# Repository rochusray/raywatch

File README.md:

# Raywatch
**An open-source, privacy-first smart(_er_)watch designed to be an all day, every day companion to help you navigate your way trugh life.**
> **Project status:** Early-stage development.

## Why Raywatch?
Most smartwatches are designed as an extension to your phone. Raywatch is build different.
## Core principles
- **Longevity:** Raywatch is meant to be a robust, long living, repairable, watertight, reliable device.
- **Independence:** Raywatch aims to be completely independent from the power grid, as well as the internet or other centralized networks.
- **Security & Privacy:** A core requirement is that Raywatch must be a secure device at all times. It will feature a [TPM](https://en.wikipedia.org/wiki/Trusted_Platform_Module), used for providing a key vault with integrated anti tampering protections, as well as encryption and decryption of sensible data and messages. Raywatch is meant to be a cryptographic fortress, build to resist. Also, Raywatch will never store or share any data without direct consent.
- **Open Source:** The Raywatch project is open source under an ethical license. Therefore it is - and will always be - open for anyone to contribute, modify or check the software and hardware.
- **Affordability:** Raywatch is aimed to be as affordable as possible. The current plan is to price it around 250€.

## Applications
- **Resistance:** Raywatch is build to not only resist against cyber attacks, but also to aid in resistance against oppression, repression, regimes and cooperations.
- **Physical Health & Disabilities:** Raywatch has multiple builtin sensors to be able to collect and analyze data about your physical health, while also never sharing it with your health insurance. It shall also provide assistance for people with disabilities.
- **Mental Health & Neurodivergents:** Raywatch started out with the purpose of tracking mental health symptoms, to detect patterns and assist therapy. This is still a prime functionality, as well as providing additional features to aid people in their lives with physical illnesses and neurodivergents.
- **Communication:** In groups, Raywatches are able to communicate via the [Meshtastic](https://meshtastic.org/) network, but separately encrypted. For maximum security it will be possible to do a local key exchange via NFC.

## Hardware Features
Here is a list of hardware features Raywatch is planned to have:
- TPM
- MicroSD card slot
- Multiple high accuracy accelerometers for acceleration and position tracking
- 3-Axis magnetometer for orientation sensing
- Heart rate & O₂ blood level sensor
- 10 buttons
- Transflective RGB LCD display
- ~60 RGB LEDs 
- BLE (_Bluetooth Low Energy_) to connect to your phone
- Meshtastic & LoRa for independend communication
- Vibration motor for discrete notifications
- 200mAh replacable battery
- NFC
- Wireless charging
- Solar powered charging

## About Us
We are a small developer collective based in Munich, Germany.
### Our Values
- **Against Discrimination:** We are completely against any kind of discrimination, including but not limited to racism, sexism, classism, ableism, and any discrimination against the LGBTQIA+ community and it's members.
- **Against Fascism:** We are openly against fascism and any fascist regime.
- **Against Exploitation:** We are strongly against any kind of exploitation of any human beings or other feeling beings.
- **Openness:** All information should be public, except private information.

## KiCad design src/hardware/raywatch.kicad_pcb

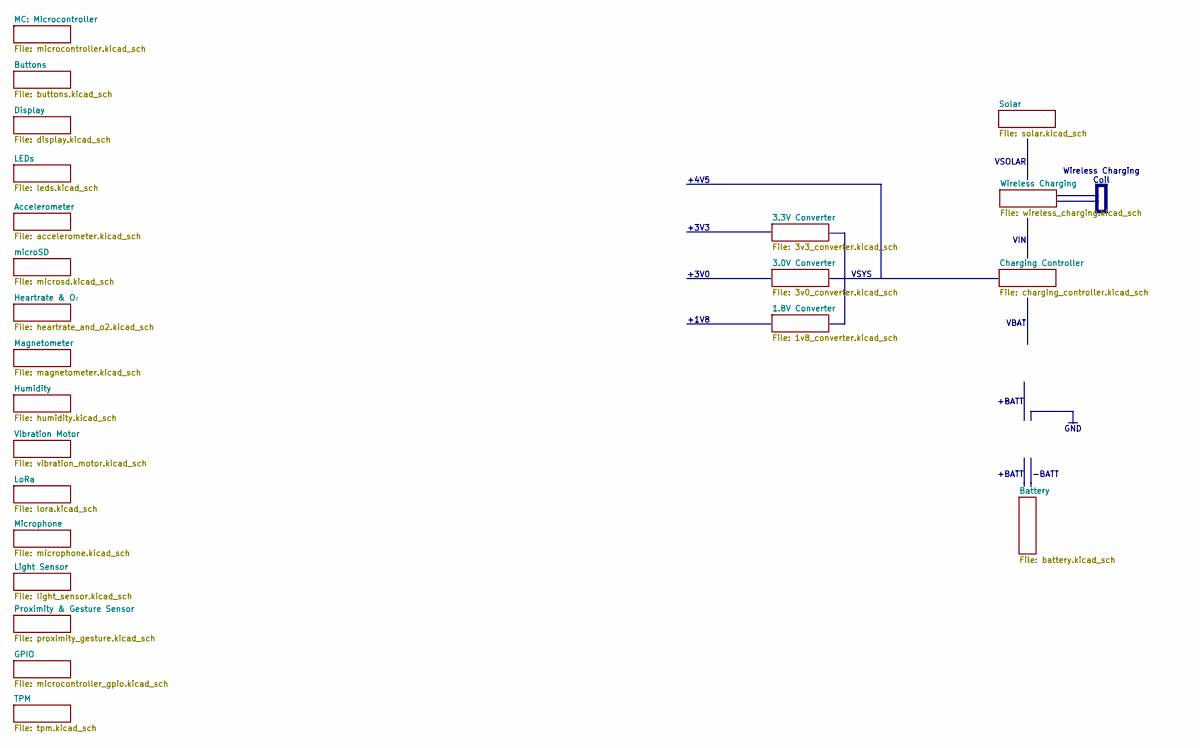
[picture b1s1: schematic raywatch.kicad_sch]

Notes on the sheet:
+BATT
-BATT
VIN
+3V0
VSOLAR
+4V5
+3V3
GND
VBAT
VSYS
+1V8
Wireless Charging Coil

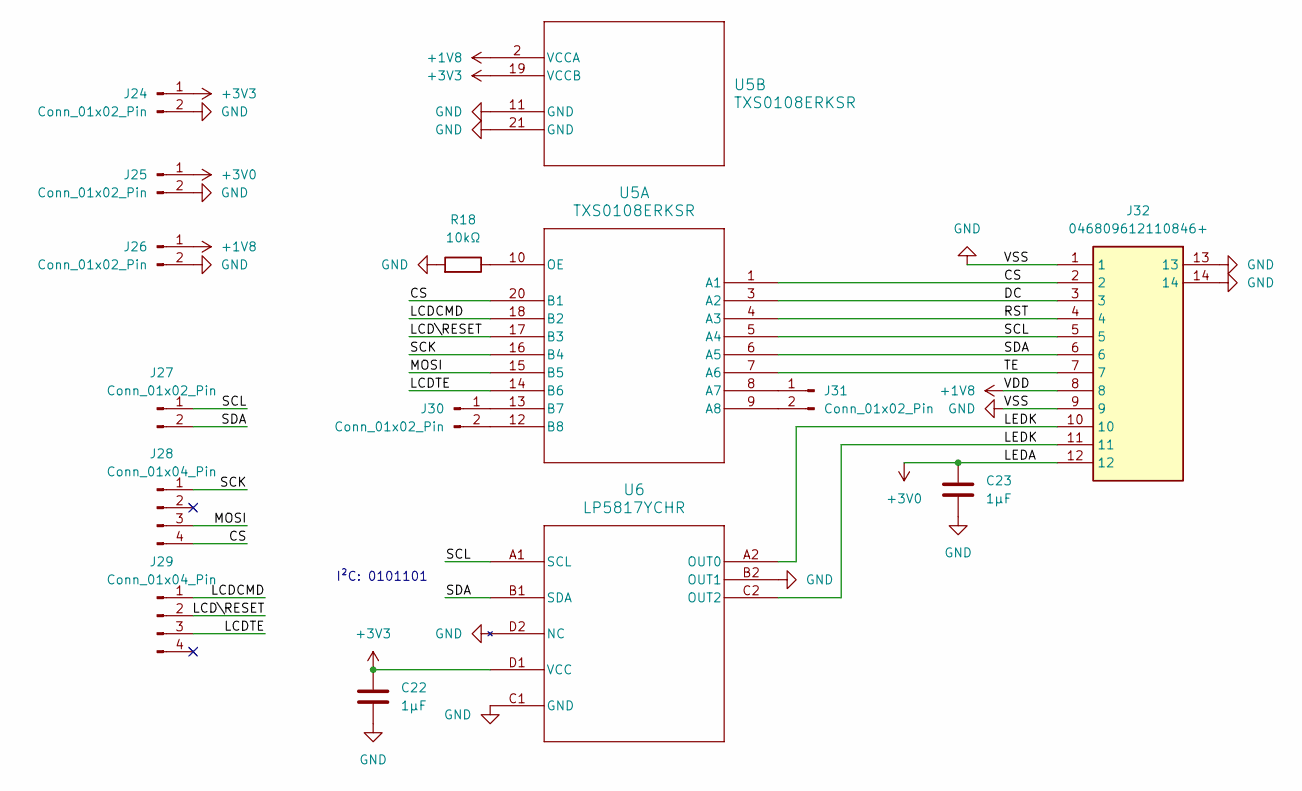
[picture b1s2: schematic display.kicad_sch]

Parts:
C22: 1µF; C_0402_1005Metric
C23: 1µF; C_0402_1005Metric; Rated voltage 10V
J24, J25, J26, J27, J30, J31: Conn_01x02_Pin; PinHeader_1x02_P1.27mm_Vertical
J28, J29: Conn_01x04_Pin; PinHeader_1x04_P1.27mm_Vertical
J32: 046809612110846+; 046809612110846; Manufacturer_Part_Number 046809612110846+; Mouser Part Number 346-046809612110846+
R18: 10kΩ; R_0402_1005Metric
U5: TXS0108ERKSR; VQFN20_RKS_TEX
U6: LP5817YCHR; DSBGA-8_YCH0008_TEX

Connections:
+3V0: C23.1, J25.1, J32.12; also elsewhere on the board
/Display/CS: J28.4, J32.2, U5.1 (A1), U5.20 (B1)
/Display/DC: J32.3, U5.3 (A2)
/Display/LCDCMD: J29.1, U5.18 (B2)
/Display/LCDTE: J29.3, U5.14 (B6)
/Display/LCD\RESET: J29.2, U5.17 (B3)
/Display/LEDK: J32.10, J32.11, U6.A2 (OUT0), U6.C2 (OUT2)
/Display/MOSI: J28.3, U5.15 (B5)
/Display/RST: J32.4, U5.4 (A3)
/Display/SCK: J28.1, U5.16 (B4)
/Display/SCL: J27.1, J32.5, U5.5 (A4), U6.A1 (SCL)
/Display/SDA: J27.2, J32.6, U5.6 (A5), U6.B1 (SDA)
/Display/TE: J32.7, U5.7 (A6)
GND: C22.2, C23.2, J24.2, J25.2, J26.2, J32.1, J32.9, J32.13, J32.14, R18.2, U5.11 (GND), U5.21 (GND), U6.B2 (OUT1), U6.C1 (GND), U6.D2 (NC); also elsewhere on the board
unnamed: J30.1, U5.13 (B7)
unnamed: J30.2, U5.12 (B8)
unnamed: J31.1, U5.8 (A7)
unnamed: J31.2, U5.9 (A8)
unnamed: R18.1, U5.10 (OE)

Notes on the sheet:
I²C: 0101101

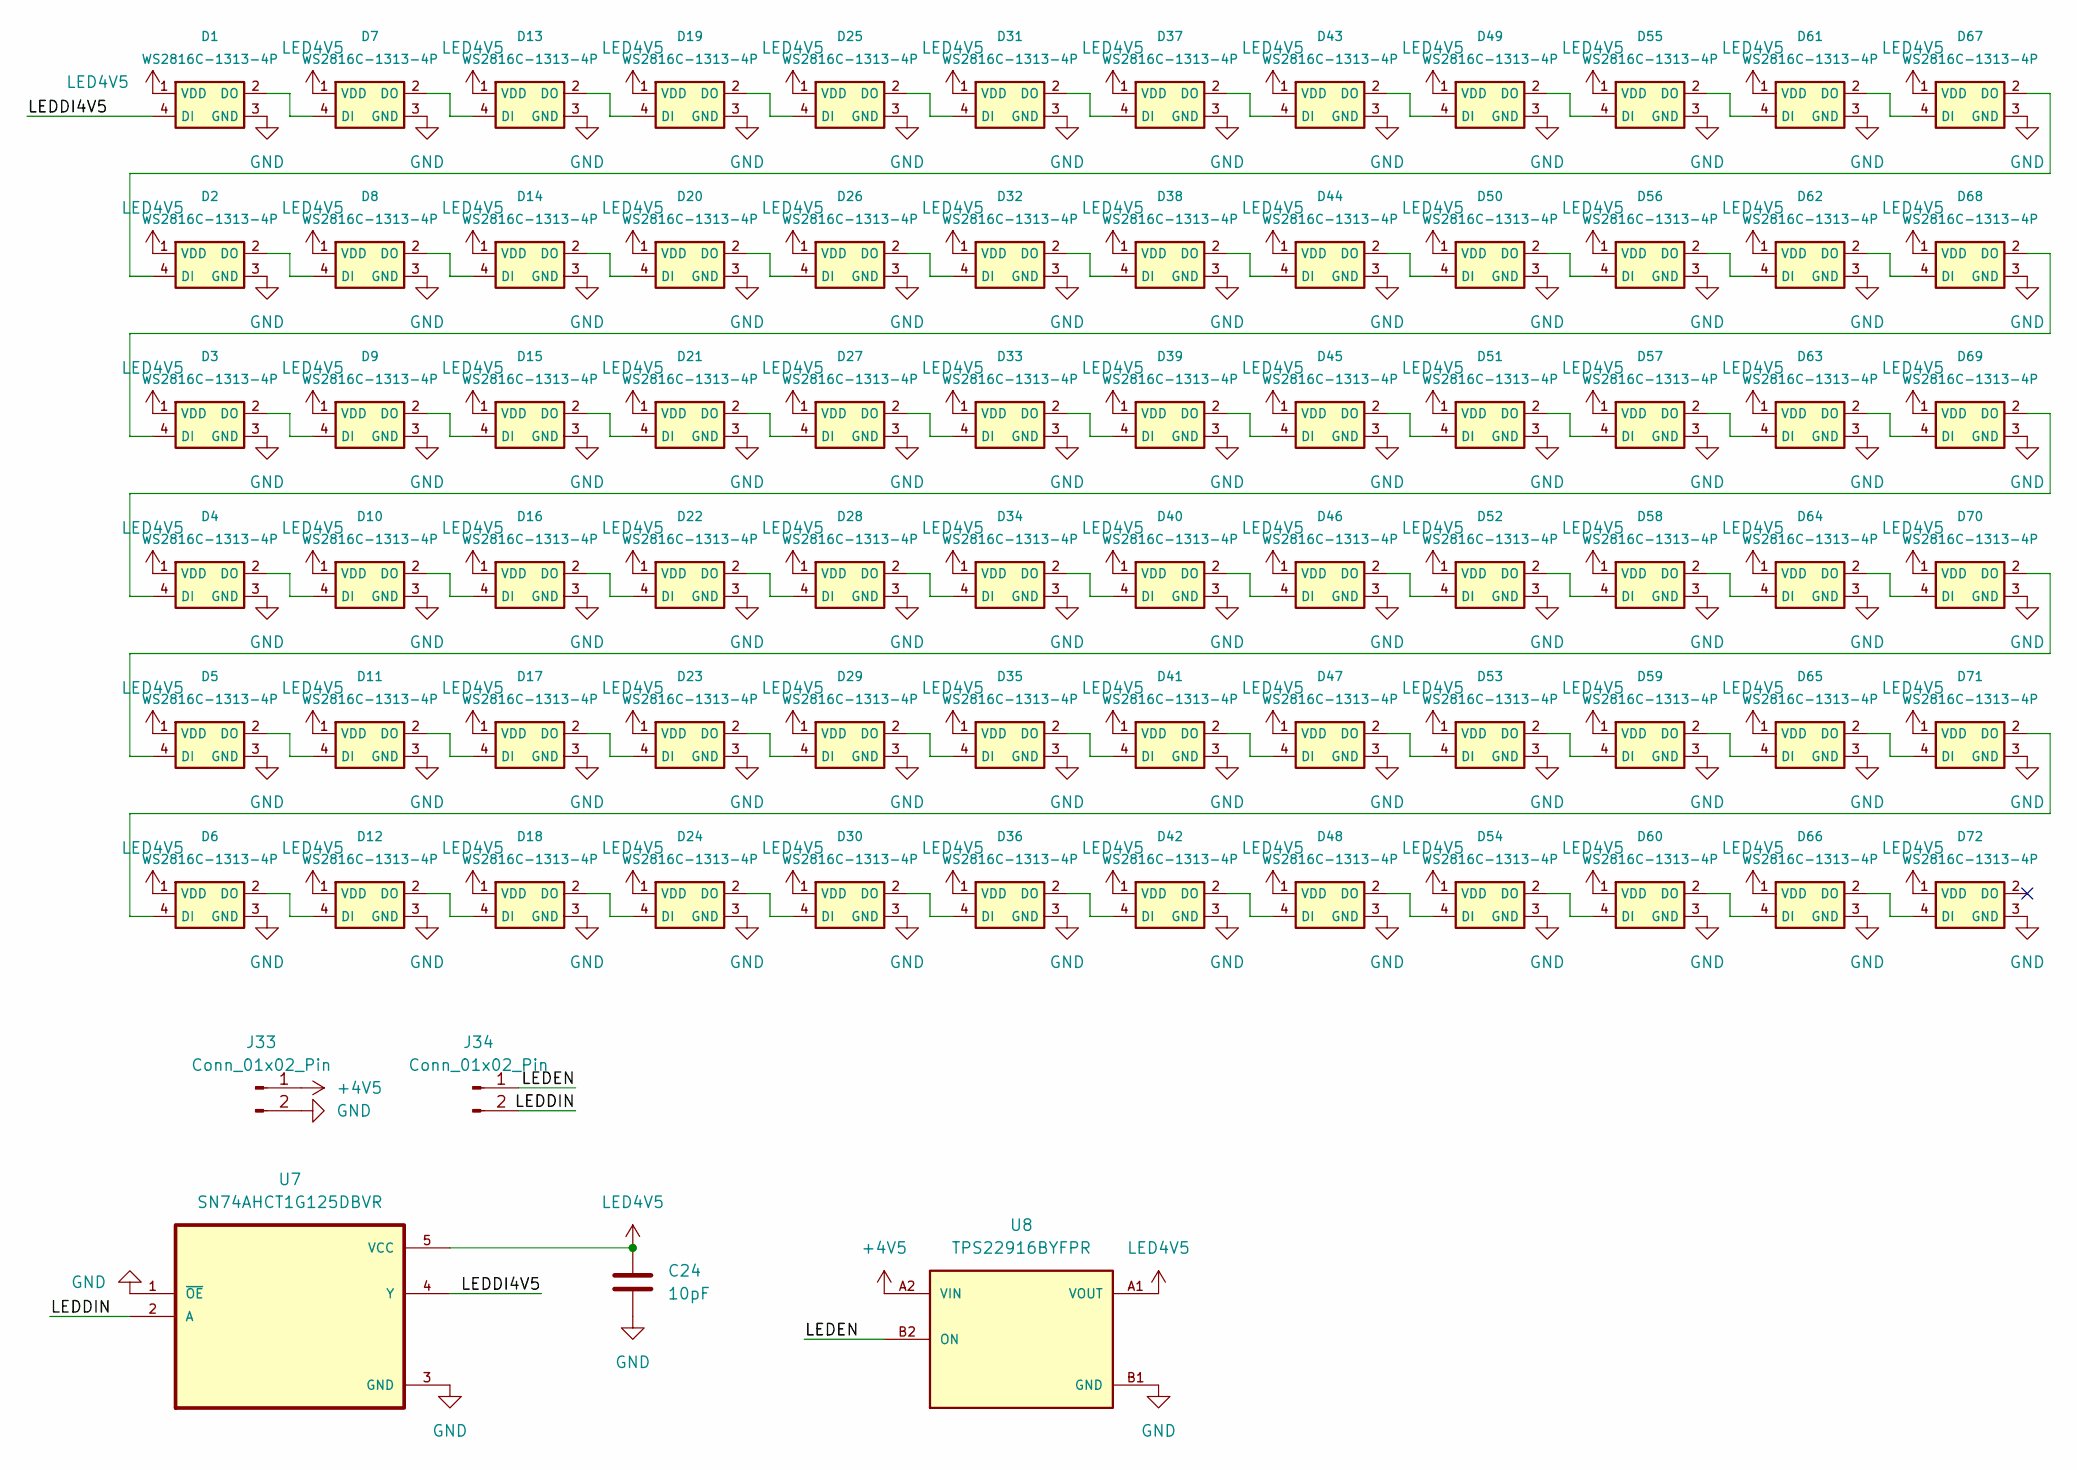
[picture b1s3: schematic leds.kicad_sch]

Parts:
C24: 10pF; C_0402_1005Metric
D1, D2, D3, D4, D5, D6, D7, D8, D9, D10, D11, D12, D13, D14, D15, D16, D17, D18, D19, D20, D21, D22, D23, D24, D25, D26, D27, D28, D29, D30, D31, D32, D33, D34, D35, D36, D37, D38, D39, D40, D41, D42, D43, D44, D45, D46, D47, D48, D49, D50, D51, D52, D53, D54, D55, D56, D57, D58, D59, D60, D61, D62, D63, D64, D65, D66, D67, D68, D69, D70, D71, D72: WS2816C-1313-4P
J33, J34: Conn_01x02_Pin; PinHeader_1x02_P1.27mm_Vertical
U7: SN74AHCT1G125DBVR; SOT95P280X145-5N
U8: TPS22916BYFPR; IC_TPS22916BYFPR; PARTREV F

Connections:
+4V5: J33.1, U8.A2 (VIN); also elsewhere on the board
/LEDs/LEDDI4V5: D1.4 (DI), U7.4 (Y)
/LEDs/LEDDIN: J34.2, U7.2 (A)
/LEDs/LEDEN: J34.1, U8.B2 (ON)
GND: C24.2, D1.3 (GND), D2.3 (GND), D3.3 (GND), D4.3 (GND), D5.3 (GND), D6.3 (GND), D7.3 (GND), D8.3 (GND), D9.3 (GND), D10.3 (GND), D11.3 (GND), D12.3 (GND), D13.3 (GND), D14.3 (GND), D15.3 (GND), D16.3 (GND), D17.3 (GND), D18.3 (GND), D19.3 (GND), D20.3 (GND), D21.3 (GND), D22.3 (GND), D23.3 (GND), D24.3 (GND), D25.3 (GND), D26.3 (GND), D27.3 (GND), D28.3 (GND), D29.3 (GND), D30.3 (GND), D31.3 (GND), D32.3 (GND), D33.3 (GND), D34.3 (GND), D35.3 (GND), D36.3 (GND), D37.3 (GND), D38.3 (GND), D39.3 (GND), D40.3 (GND), D41.3 (GND), D42.3 (GND), D43.3 (GND), D44.3 (GND), D45.3 (GND), D46.3 (GND), D47.3 (GND), D48.3 (GND), D49.3 (GND), D50.3 (GND), D51.3 (GND), D52.3 (GND), D53.3 (GND), D54.3 (GND), D55.3 (GND), D56.3 (GND), D57.3 (GND), D58.3 (GND), D59.3 (GND), D60.3 (GND), D61.3 (GND), D62.3 (GND), D63.3 (GND), D64.3 (GND), D65.3 (GND), D66.3 (GND), D67.3 (GND), D68.3 (GND), D69.3 (GND), D70.3 (GND), D71.3 (GND), D72.3 (GND), J33.2, U7.1 (~OE), U7.3 (GND), U8.B1 (GND); also elsewhere on the board
LED4V5: C24.1, D1.1 (VDD), D2.1 (VDD), D3.1 (VDD), D4.1 (VDD), D5.1 (VDD), D6.1 (VDD), D7.1 (VDD), D8.1 (VDD), D9.1 (VDD), D10.1 (VDD), D11.1 (VDD), D12.1 (VDD), D13.1 (VDD), D14.1 (VDD), D15.1 (VDD), D16.1 (VDD), D17.1 (VDD), D18.1 (VDD), D19.1 (VDD), D20.1 (VDD), D21.1 (VDD), D22.1 (VDD), D23.1 (VDD), D24.1 (VDD), D25.1 (VDD), D26.1 (VDD), D27.1 (VDD), D28.1 (VDD), D29.1 (VDD), D30.1 (VDD), D31.1 (VDD), D32.1 (VDD), D33.1 (VDD), D34.1 (VDD), D35.1 (VDD), D36.1 (VDD), D37.1 (VDD), D38.1 (VDD), D39.1 (VDD), D40.1 (VDD), D41.1 (VDD), D42.1 (VDD), D43.1 (VDD), D44.1 (VDD), D45.1 (VDD), D46.1 (VDD), D47.1 (VDD), D48.1 (VDD), D49.1 (VDD), D50.1 (VDD), D51.1 (VDD), D52.1 (VDD), D53.1 (VDD), D54.1 (VDD), D55.1 (VDD), D56.1 (VDD), D57.1 (VDD), D58.1 (VDD), D59.1 (VDD), D60.1 (VDD), D61.1 (VDD), D62.1 (VDD), D63.1 (VDD), D64.1 (VDD), D65.1 (VDD), D66.1 (VDD), D67.1 (VDD), D68.1 (VDD), D69.1 (VDD), D70.1 (VDD), D71.1 (VDD), D72.1 (VDD), U7.5 (VCC), U8.A1 (VOUT)
unnamed: D1.2 (DO), D7.4 (DI)
unnamed: D2.4 (DI), D67.2 (DO)
unnamed: D2.2 (DO), D8.4 (DI)
unnamed: D3.4 (DI), D68.2 (DO)
unnamed: D3.2 (DO), D9.4 (DI)
unnamed: D4.4 (DI), D69.2 (DO)
unnamed: D5.4 (DI), D70.2 (DO)
unnamed: D6.4 (DI), D71.2 (DO)
unnamed: D4.2 (DO), D10.4 (DI)
unnamed: D10.2 (DO), D16.4 (DI)
unnamed: D5.2 (DO), D11.4 (DI)
unnamed: D11.2 (DO), D17.4 (DI)
unnamed: D6.2 (DO), D12.4 (DI)
unnamed: D12.2 (DO), D18.4 (DI)
unnamed: D7.2 (DO), D13.4 (DI)
unnamed: D13.2 (DO), D19.4 (DI)
unnamed: D8.2 (DO), D14.4 (DI)
unnamed: D14.2 (DO), D20.4 (DI)
unnamed: D9.2 (DO), D15.4 (DI)
unnamed: D15.2 (DO), D21.4 (DI)
unnamed: D16.2 (DO), D22.4 (DI)
unnamed: D17.2 (DO), D23.4 (DI)
unnamed: D18.2 (DO), D24.4 (DI)
unnamed: D19.2 (DO), D25.4 (DI)
unnamed: D20.2 (DO), D26.4 (DI)
unnamed: D21.2 (DO), D27.4 (DI)
unnamed: D22.2 (DO), D28.4 (DI)
unnamed: D23.2 (DO), D29.4 (DI)
unnamed: D24.2 (DO), D30.4 (DI)
unnamed: D25.2 (DO), D31.4 (DI)
unnamed: D26.2 (DO), D32.4 (DI)
unnamed: D27.2 (DO), D33.4 (DI)
unnamed: D28.2 (DO), D34.4 (DI)
unnamed: D29.2 (DO), D35.4 (DI)
unnamed: D30.2 (DO), D36.4 (DI)
unnamed: D31.2 (DO), D37.4 (DI)
unnamed: D32.2 (DO), D38.4 (DI)
unnamed: D33.2 (DO), D39.4 (DI)
unnamed: D34.2 (DO), D40.4 (DI)
unnamed: D35.2 (DO), D41.4 (DI)
unnamed: D36.2 (DO), D42.4 (DI)
unnamed: D37.2 (DO), D43.4 (DI)
unnamed: D38.2 (DO), D44.4 (DI)
unnamed: D39.2 (DO), D45.4 (DI)
unnamed: D40.2 (DO), D46.4 (DI)
unnamed: D41.2 (DO), D47.4 (DI)
unnamed: D42.2 (DO), D48.4 (DI)
unnamed: D43.2 (DO), D49.4 (DI)
unnamed: D44.2 (DO), D50.4 (DI)
unnamed: D45.2 (DO), D51.4 (DI)
unnamed: D46.2 (DO), D52.4 (DI)
unnamed: D47.2 (DO), D53.4 (DI)
unnamed: D48.2 (DO), D54.4 (DI)
unnamed: D49.2 (DO), D55.4 (DI)
unnamed: D50.2 (DO), D56.4 (DI)
unnamed: D51.2 (DO), D57.4 (DI)
unnamed: D52.2 (DO), D58.4 (DI)
unnamed: D53.2 (DO), D59.4 (DI)
unnamed: D54.2 (DO), D60.4 (DI)
unnamed: D55.2 (DO), D61.4 (DI)
unnamed: D56.2 (DO), D62.4 (DI)
unnamed: D57.2 (DO), D63.4 (DI)
unnamed: D58.2 (DO), D64.4 (DI)
unnamed: D59.2 (DO), D65.4 (DI)
unnamed: D60.2 (DO), D66.4 (DI)
unnamed: D61.2 (DO), D67.4 (DI)
unnamed: D62.2 (DO), D68.4 (DI)
unnamed: D63.2 (DO), D69.4 (DI)
unnamed: D64.2 (DO), D70.4 (DI)
unnamed: D65.2 (DO), D71.4 (DI)
unnamed: D66.2 (DO), D72.4 (DI)

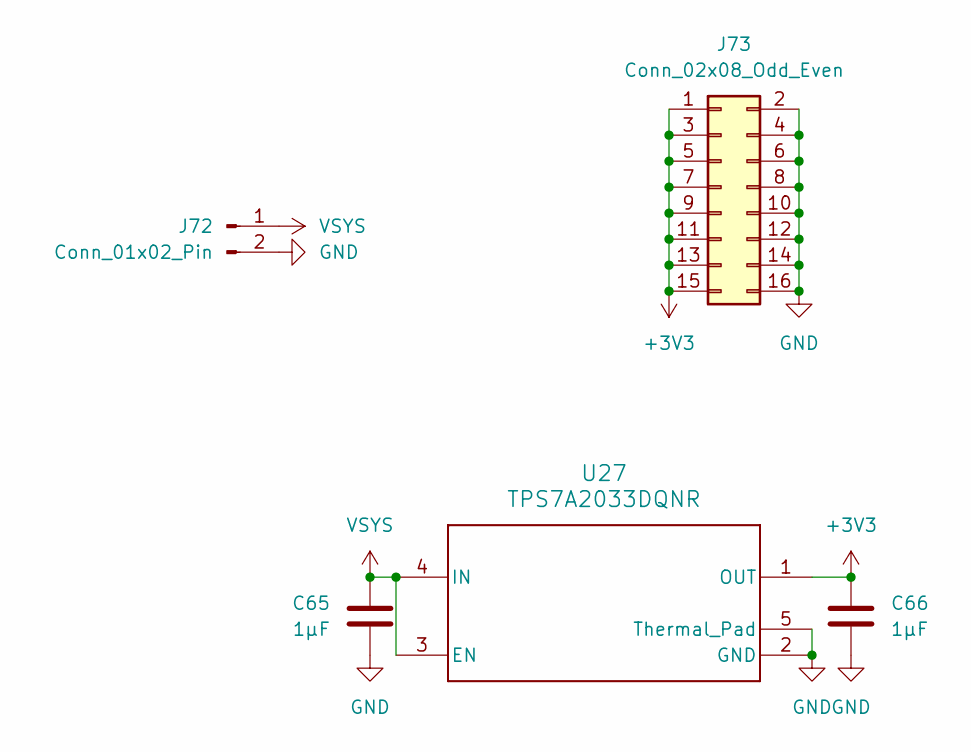
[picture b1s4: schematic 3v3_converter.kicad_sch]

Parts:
C65, C66: 1µF; C_0402_1005Metric
J72: Conn_01x02_Pin; PinHeader_1x02_P1.27mm_Vertical
J73: Conn_02x08_Odd_Even; PinHeader_2x08_P1.27mm_Vertical
U27: TPS7A2033DQNR; DQN0004A-MFG

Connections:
+4V5: C65.1, J72.1, U27.3 (EN), U27.4 (IN); also elsewhere on the board
GND: C65.2, C66.2, J72.2, J73.2, J73.4, J73.6, J73.8, J73.10, J73.12, J73.14, J73.16, U27.2 (GND), U27.5 (Thermal_Pad); also elsewhere on the board

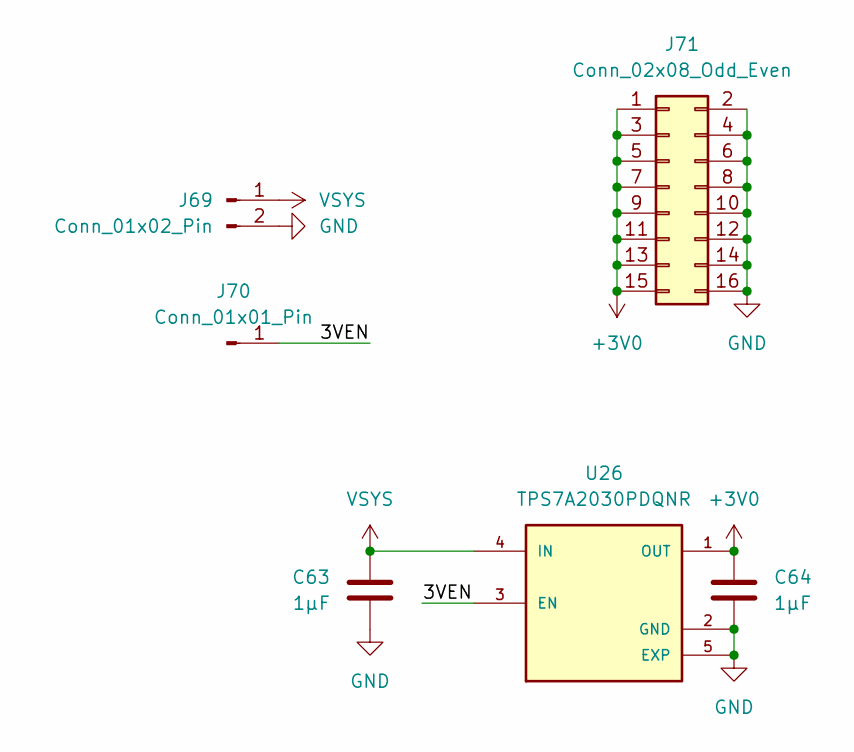
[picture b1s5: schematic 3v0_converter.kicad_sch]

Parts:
C63, C64: 1µF; C_0402_1005Metric
J69: Conn_01x02_Pin; PinHeader_1x02_P1.27mm_Vertical
J70: Conn_01x01_Pin; PinHeader_1x01_P1.27mm_Vertical
J71: Conn_02x08_Odd_Even; PinHeader_2x08_P1.27mm_Vertical
U26: TPS7A2030PDQNR; VREG_TPS7A2030PDQNR; PARTREV H

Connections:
+3V0: C64.1, J71.1, J71.3, J71.5, J71.7, J71.9, J71.11, J71.13, J71.15, U26.1 (OUT); also elsewhere on the board
+4V5: C63.1, J69.1, U26.4 (IN); also elsewhere on the board
/3.0V Converter/3VEN: J70.1, U26.3 (EN)
GND: C63.2, C64.2, J69.2, J71.2, J71.4, J71.6, J71.8, J71.10, J71.12, J71.14, J71.16, U26.2 (GND), U26.5 (EXP); also elsewhere on the board

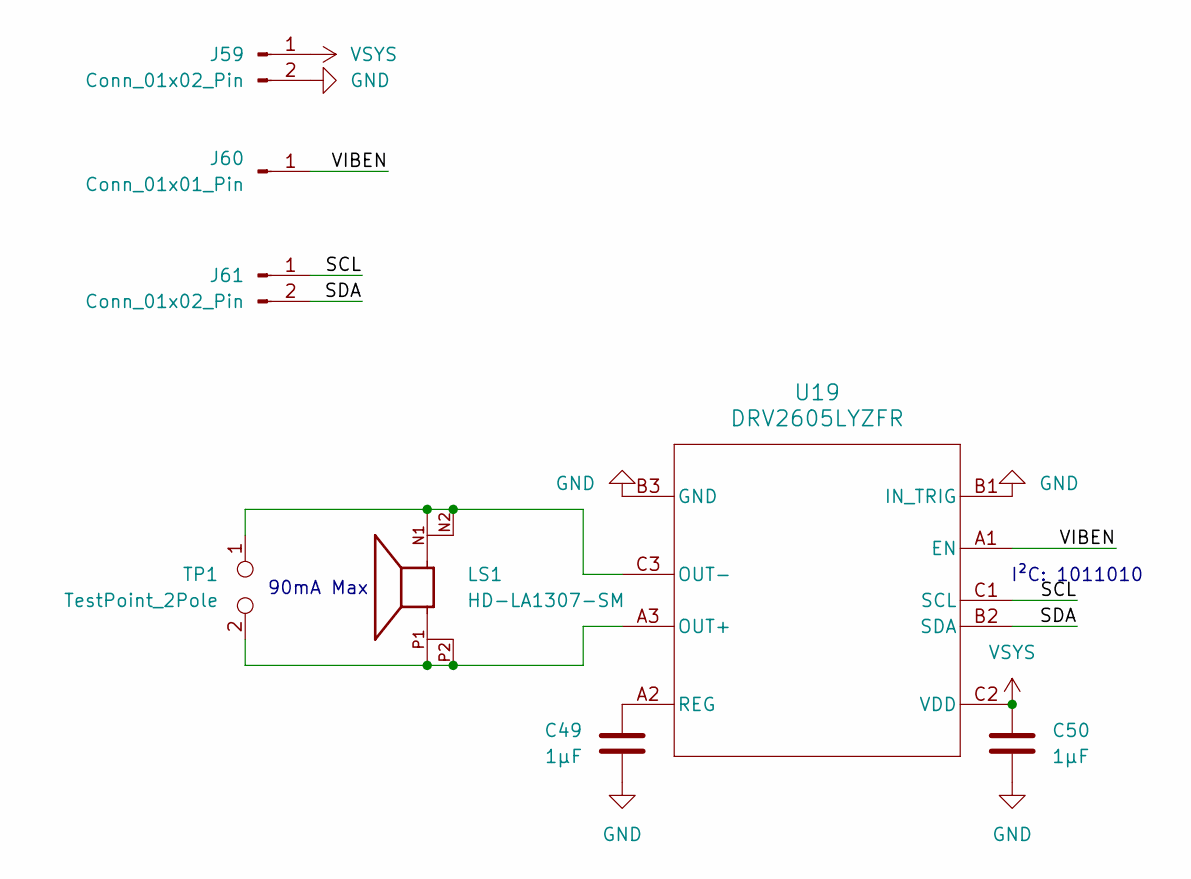
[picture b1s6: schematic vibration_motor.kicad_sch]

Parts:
C49, C50: 1µF; C_0402_1005Metric
J59, J61: Conn_01x02_Pin; PinHeader_1x02_P1.27mm_Vertical
J60: Conn_01x01_Pin; PinHeader_1x01_P1.27mm_Vertical
LS1: HD-LA1307-SM; XDCR_HD-LA1307-SM; PARTREV A; DigiKey_Part_Number 668-HD-LA1307-SMCT-ND
TP1: TestPoint_2Pole; TestPoint_2Pads_Pitch2.54mm_Drill0.8mm
U19: DRV2605LYZFR; YZF0009ADAD

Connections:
+4V5: C50.1, J59.1, U19.C2 (VDD); also elsewhere on the board
/Vibration Motor/SCL: J61.1, U19.C1 (SCL)
/Vibration Motor/SDA: J61.2, U19.B2 (SDA)
/Vibration Motor/VIBEN: J60.1, U19.A1 (EN)
GND: C49.2, C50.2, J59.2, U19.B1 (IN_TRIG), U19.B3 (GND); also elsewhere on the board
unnamed: LS1.P1, LS1.P2, TP1.2, U19.A3 (OUT+)
unnamed: LS1.N1, LS1.N2, TP1.1, U19.C3 (OUT-)
unnamed: C49.1, U19.A2 (REG)

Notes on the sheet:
I²C: 1011010
90mA Max

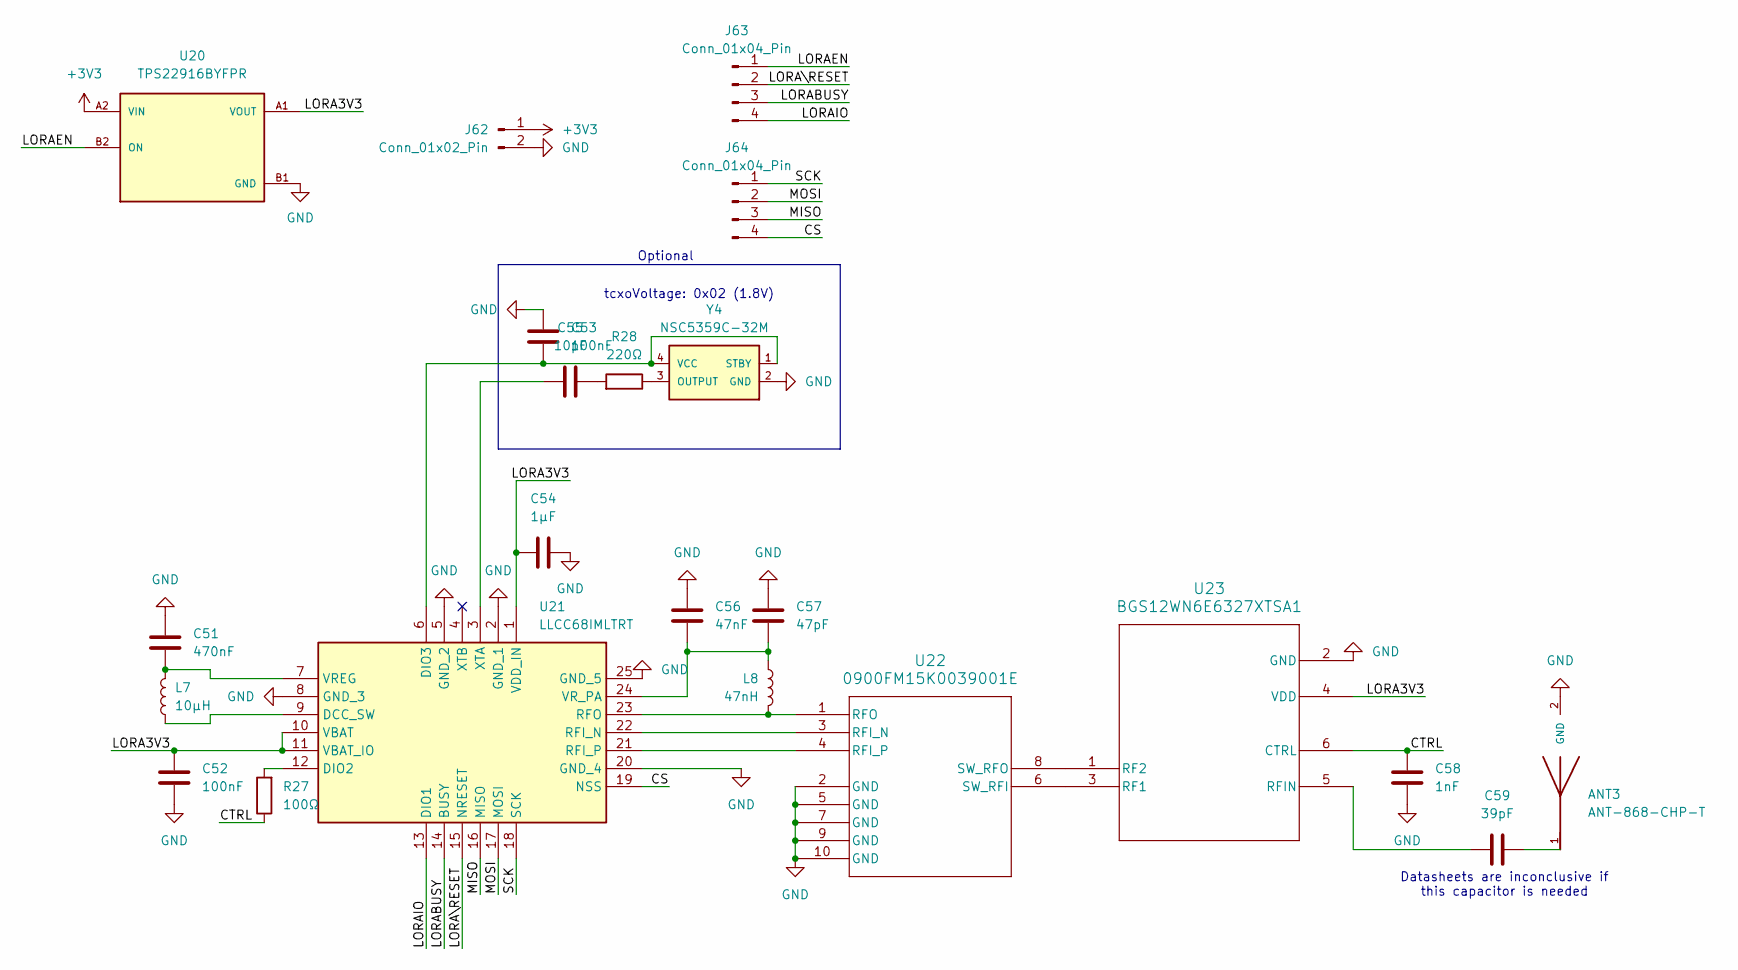
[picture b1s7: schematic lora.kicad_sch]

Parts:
ANT3: ANT-868-CHP-T; XDCR_ANT-868-CHP-T; PARTREV C
C51: 470nF; C_0402_1005Metric; Tolerance 10%; Max Voltage 10V
C52: 100nF; C_0402_1005Metric; Tolerance 10%; Max Voltage 10V
C53: 100nF; C_0402_1005Metric
C54: 1µF; C_0402_1005Metric; Tolerance 10%; Max Voltage 10V
C55: 10pF; C_0402_1005Metric
C56: 47nF; C_0402_1005Metric; Tolerance 10%; Max Voltage 16V
C57: 47pF; C_0402_1005Metric; Tolerance 5%; Max Voltage 50V
C58: 1nF; C_0402_1005Metric; Tolerance 10%; Max Voltage 50V
C59: 39pF; C_0402_1005Metric; Tolerance 5%; Max Voltage 50V
J62: Conn_01x02_Pin; PinHeader_1x02_P1.27mm_Vertical
J63, J64: Conn_01x04_Pin; PinHeader_1x04_P1.27mm_Vertical
L7: 10µH; L_0402_1005Metric; Tolerance 5%
L8: 47nH; L_0402_1005Metric; Tolerance 5%
R27: 100Ω; R_0402_1005Metric
R28: 220Ω; R_0402_1005Metric
U20: TPS22916BYFPR; IC_TPS22916BYFPR; PARTREV F
U21: LLCC68IMLTRT; QFN50P400X400X100-25L-D; Mouser Part Number 947-LLCC68IMLTRT
U22: 0900FM15K0039001E; QFP20P0X0X31-0_JOT
U23: BGS12WN6E6327XTSA1; PG-TSNP-6-10_INF
Y4: NSC5359C-32M; NSC5359C

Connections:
/LoRa/CS: J64.4, U21.19 (NSS)
/LoRa/CTRL: C58.2, R27.1, U23.6 (CTRL)
/LoRa/LORA3V3: C52.1, C54.1, U20.A1 (VOUT), U21.1 (VDD_IN), U21.10 (VBAT), U21.11 (VBAT_IO), U23.4 (VDD)
/LoRa/LORABUSY: J63.3, U21.14 (BUSY)
/LoRa/LORAEN: J63.1, U20.B2 (ON)
/LoRa/LORAIO: J63.4, U21.13 (DIO1)
/LoRa/LORA\RESET: J63.2, U21.15 (NRESET)
/LoRa/MISO: J64.3, U21.16 (MISO)
/LoRa/MOSI: J64.2, U21.17 (MOSI)
/LoRa/SCK: J64.1, U21.18 (SCK)
GND: ANT3.2 (GND), C51.1, C52.2, C53.1, C54.2, C56.1, C57.1, C58.1, J62.2, U20.B1 (GND), U21.2 (GND_1), U21.5 (GND_2), U21.8 (GND_3), U21.20 (GND_4), U21.25 (GND_5), U22.2 (GND), U22.5 (GND), U22.7 (GND), U22.9 (GND), U22.10 (GND), U23.2 (GND), Y4.2 (GND); also elsewhere on the board
unnamed: ANT3.1, C59.1
unnamed: C55.1, R28.2
unnamed: L7.1, U21.9 (DCC_SW)
unnamed: R27.2, U21.12 (DIO2)
unnamed: C53.2, U21.6 (DIO3), Y4.1 (STBY), Y4.4 (VCC)
unnamed: U21.22 (RFI_N), U22.3 (RFI_N)
unnamed: U21.21 (RFI_P), U22.4 (RFI_P)
unnamed: L8.2, U21.23 (RFO), U22.1 (RFO)
unnamed: C51.2, L7.2, U21.7 (VREG)
unnamed: C56.2, C57.2, L8.1, U21.24 (VR_PA)
unnamed: C55.2, U21.3 (XTA)
unnamed: U22.6 (SW_RFI), U23.3 (RF1)
unnamed: U22.8 (SW_RFO), U23.1 (RF2)
unnamed: C59.2, U23.5 (RFIN)
unnamed: R28.1, Y4.3 (OUTPUT)

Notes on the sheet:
Datasheets are inconclusive if this capacitor is needed
tcxoVoltage: 0x02 (1.8V)
Optional

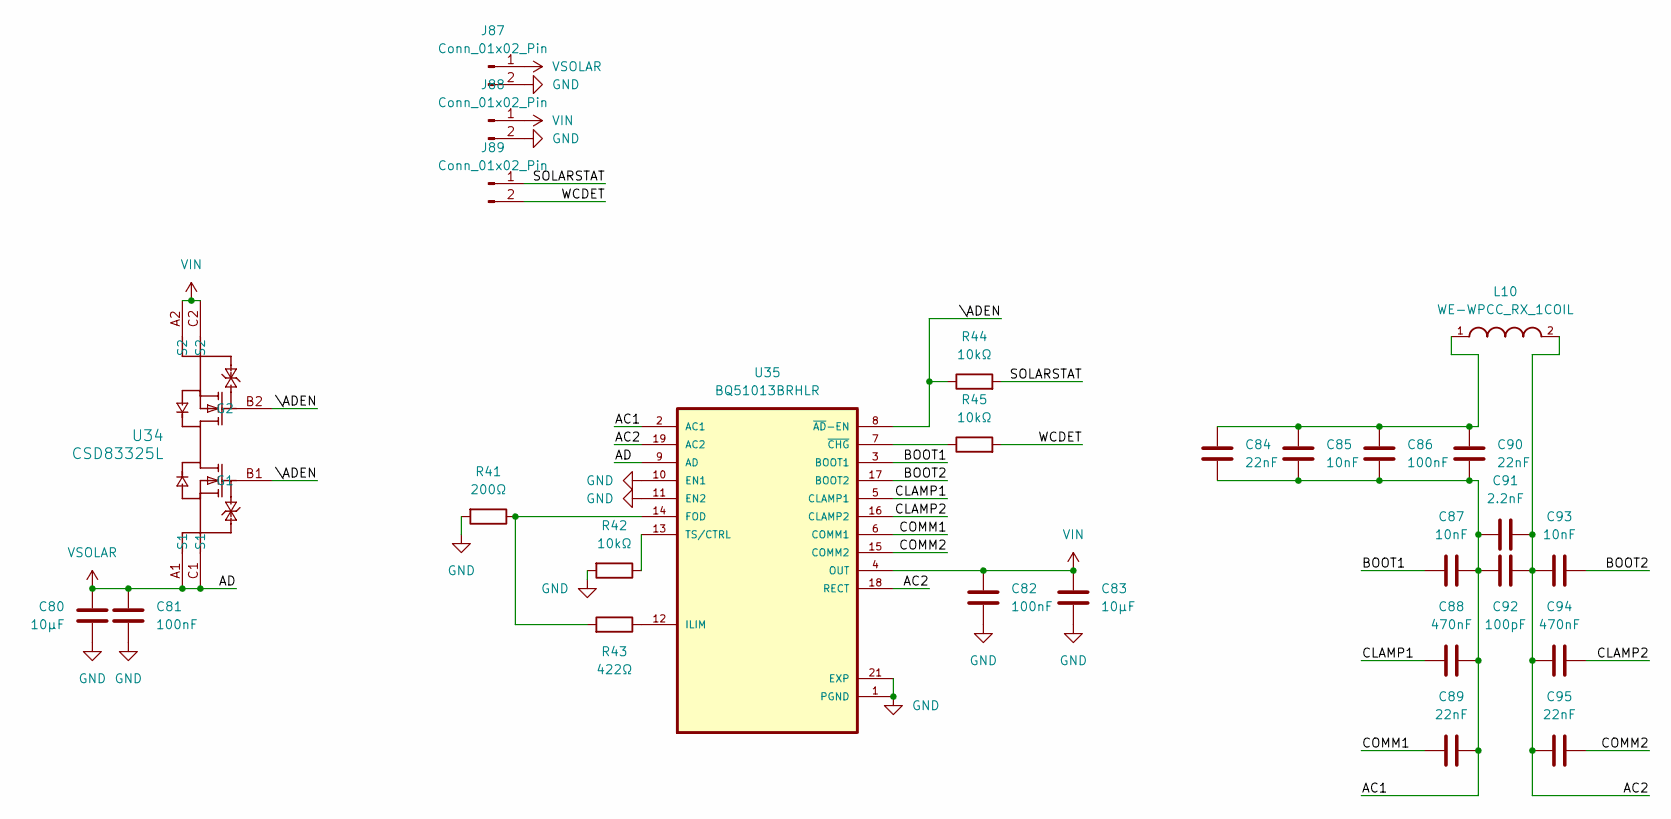
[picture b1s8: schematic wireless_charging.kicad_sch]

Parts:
C80, C83: 10µF; C_0402_1005Metric
C81, C82: 100nF; C_0402_1005Metric
C84, C89, C90: 22nF; C_0402_1005Metric; Max Voltage 25V
C85, C87: 10nF; C_0402_1005Metric; Max Voltage 25V
C86: 100nF; C_0402_1005Metric; Max Voltage 25V
C88: 470nF; C_0402_1005Metric; Max Voltage 25V
C91: 2.2nF; C_0402_1005Metric
C92: 100pF; C_0402_1005Metric
C93: 10nF; C_0402_1005Metric
C94: 470nF; C_0402_1005Metric
C95: 22nF; C_0402_1005Metric
J87, J88, J89: Conn_01x02_Pin; PinHeader_1x02_P1.27mm_Vertical
L10: WE-WPCC_RX_1COIL; WE-WPCC_RX_760308103205; DigiKey_Part_Number 732-6210-ND
R41: 200Ω; R_0402_1005Metric
R42, R44, R45: 10kΩ; R_0402_1005Metric
R43: 422Ω; R_0402_1005Metric
U34: CSD83325L; YJE0006A
U35: BQ51013BRHLR; IC_MSP430FR2522IRHLR

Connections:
/Wireless Charging/AC1: C84.1, C85.1, C86.1, C87.2, C88.2, C89.2, C90.1, C91.1, C92.1, U35.2 (AC1)
/Wireless Charging/AC2: C91.2, C92.2, C93.2, C94.2, C95.2, L10.2, U35.18 (RECT), U35.19 (AC2)
/Wireless Charging/BOOT1: C87.1, U35.3 (BOOT1)
/Wireless Charging/BOOT2: C93.1, U35.17 (BOOT2)
/Wireless Charging/CLAMP1: C88.1, U35.5 (CLAMP1)
/Wireless Charging/CLAMP2: C94.1, U35.16 (CLAMP2)
/Wireless Charging/COMM1: C89.1, U35.6 (COMM1)
/Wireless Charging/COMM2: C95.1, U35.15 (COMM2)
/Wireless Charging/SOLARSTAT: J89.1, R44.2
/Wireless Charging/WCDET: J89.2, R45.2
/Wireless Charging/\ADEN: R44.1, U34.B1 (G1), U34.B2 (G2), U35.8 (~AD-EN)
GND: C80.1, C81.1, C82.2, C83.2, J87.2, J88.2, R41.2, R42.2, U35.1 (PGND), U35.10 (EN1), U35.11 (EN2), U35.20 (PGND), U35.21 (EXP), U35.22 (EXP), U35.23 (EXP), U35.24 (EXP), U35.25 (EXP), U35.26 (EXP), U35.27 (EXP), U35.28 (EXP), U35.29 (EXP); also elsewhere on the board
unnamed: C84.2, C85.2, C86.2, C90.2, L10.1
unnamed: R41.1, R43.2, U35.14 (FOD)
unnamed: R43.1, U35.12 (ILIM)
unnamed: R42.1, U35.13 (TS/CTRL)
unnamed: R45.1, U35.7 (~CHG)
VIN: C82.1, C83.1, J88.1, U34.A2 (S2), U34.C2 (S2), U35.4 (OUT); also elsewhere on the board
VSOLAR: C80.2, C81.2, J87.1, U34.A1 (S1), U34.C1 (S1), U35.9 (AD); also elsewhere on the board

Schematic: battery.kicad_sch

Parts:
C67: 1µF; C_0402_1005Metric
C68: 100µF; C_0402_1005Metric
C69: 470nF; C_0402_1005Metric
C70: 2.2µF; C_0402_1005Metric
J74: BM29B0.6-2DS/2-0.35V51; CONN_BM29B0.6-2DS&slash_2-0.35V51_HIR
J75, J76, J77, J78: Conn_01x02_Pin; PinHeader_1x02_P1.27mm_Vertical
J79: Conn_01x04_Pin; PinHeader_1x04_P1.27mm_Vertical
R29: 330Ω; R_0402_1005Metric
R30, R31: 10kΩ; R_0402_1005Metric
R32: 2.2kΩ; R_0402_1005Metric
R33: 10mΩ; R_0402_1005Metric; Tolerance 1%
U28: BQ27426YZFR; IC_BQ27421YZFR-G1A
U29: BQ29700DSER; SON50P150X150X80-6N; PARTREV G
U30: CSD83325L; YJE0006A

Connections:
+1V8: C69.2, C70.2, J75.1, R30.1, U28.B3 (VDD); also elsewhere on the board
+BATT: C67.2, J74.P1_1, J74.P1_2, J79.3, R29.1, R33.1, U28.C1 (SRP), U28.C3 (BAT)
-BATT: C68.2, J74.P2_1, J74.P2_2, J79.4, U29.4 (VSS), U30.A1 (S1), U30.C1 (S1)
/Battery/BATTERM: J74.S1, J78.1, J79.1
/Battery/SCL1V8: J77.1, U28.A3 (SCL)
/Battery/SDA1V8: J77.2, U28.A2 (SDA)
GND: C67.1, C69.1, C70.1, J74.S2, J75.2, J76.2, J78.2, J79.2, R31.1, R32.1, U28.B2 (VSS), U30.A2 (S2), U30.C2 (S2); also elsewhere on the board
unnamed: R31.2, U28.B1 (BIN)
unnamed: R30.2, U28.A1 (GPOUT)
unnamed: C68.1, R29.2, U29.5 (BAT)
unnamed: U29.2 (COUT), U30.B2 (G2)
unnamed: U29.3 (DOUT), U30.B1 (G1)
unnamed: R32.2, U29.6 (V-)
VBAT: J76.1, R33.2, U28.C2 (SRN); also elsewhere on the board

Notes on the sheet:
Protection
Gauge
Battery: CS-OPW190SH
Battery Connector Reference
I²C: 1010101
NTC Thermistor 10k
P1 BATT+
P2 BATT-

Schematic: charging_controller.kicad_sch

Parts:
C71, C75, C76: 10µF; C_0402_1005Metric
C72, C73, C74: 1µF; C_0402_1005Metric
J80, J84: Conn_01x02_Pin; PinHeader_1x02_P1.27mm_Vertical
J81: Conn_01x04_Pin; PinHeader_1x04_P1.27mm_Vertical
J82, J83: Conn_02x08_Odd_Even; PinHeader_2x08_P1.27mm_Vertical
J85: Conn_01x01_Pin; PinHeader_1x01_P1.27mm_Vertical
R34: 43kΩ; R_0402_1005Metric
R35, R36: 10kΩ; R_0402_1005Metric
R37, R38: 2.2kΩ; R_0402_1005Metric
U31: TPS22916BYFPR; IC_TPS22916BYFPR; PARTREV F
U32: BQ25185DLHR; IC_BQ25185DLHR; PARTREV OCTOBER 2023

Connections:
+4V5: C73.2, C75.2, J82.1, J82.3, J82.5, J82.7, J82.9, J82.11, J82.13, J82.15, J83.1, J83.3, J83.5, J83.7, J83.9, J83.11, J83.13, J83.15, U32.1 (SYS); also elsewhere on the board
/Charging Controller/BATTERM: J85.1, U32.6 (TS/MR)
/Charging Controller/CHARGESTAT1: J81.3, R35.2, U32.9 (STAT1)
/Charging Controller/CHARGESTAT2: J81.4, R36.2, U32.3 (STAT2)
/Charging Controller/FASTCHARGE: J81.1, U31.B2 (ON)
/Charging Controller/\ENCHARGE: J81.2, U32.4 (~CE)
GND: C71.1, C72.1, C73.1, C74.1, C75.1, C76.1, J80.2, J82.2, J82.4, J82.6, J82.8, J82.10, J82.12, J82.14, J82.16, J83.2, J83.4, J83.6, J83.8, J83.10, J83.12, J83.14, J83.16, J84.2, R34.1, R37.2, U31.A1 (VOUT), U31.B1 (GND), U32.5 (GND), U32.11 (THERMAL_PAD); also elsewhere on the board
unnamed: R37.1, R38.2, U31.A2 (VIN)
unnamed: R34.2, U32.7 (ILIM/VSET)
unnamed: R38.1, U32.8 (ISET)
VBAT: C74.2, C76.2, J84.1, U32.2 (BAT); also elsewhere on the board
VIN: C71.2, C72.2, J80.1, U32.10 (IN); also elsewhere on the board

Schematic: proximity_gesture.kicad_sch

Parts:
C97, C99, C100, C101, C102: 100nF; C_0402_1005Metric
C98, C103, C104, C106, C108: 1µF; C_0402_1005Metric
C105, C107: 10µF; C_0402_1005Metric
D73: VSMY2850G; DIO_VSMY2850G; PARTREV 1.5
J92, J93, J94, J95: Conn_01x02_Pin; PinHeader_1x02_P1.27mm_Vertical
J96: Conn_01x04_Pin; PinHeader_1x04_P1.27mm_Vertical
R46: 10kΩ; R_0402_1005Metric
U37: APDS-9500; ADPS-9500
Y5: SG-210STF_24.0000ML0; OSC_SG-210STF_24.0000ML0; PARTREV 2025/6/18

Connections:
+4V5: C105.1, C106.1, C107.1, C108.1, D73.A, J93.1, U37.9 (LED-A); also elsewhere on the board
/Proximity & Gesture Sensor/CS: J96.4, U37.16 (SPI_CS)
/Proximity & Gesture Sensor/IRCLKEN: J94.2, Y5.1 (~ST)
/Proximity & Gesture Sensor/IRINT: J94.1, R46.2, U37.2 (INT)
/Proximity & Gesture Sensor/MISO: J96.3, U37.4 (SPI_DATA)
/Proximity & Gesture Sensor/SCK: J96.1, U37.5 (SPI_CLK)
/Proximity & Gesture Sensor/SCL: J95.1, U37.18 (I2C_SCL)
/Proximity & Gesture Sensor/SDA: J95.2, U37.17 (I2C_SDA)
/Proximity & Gesture Sensor/SPIMCLK: U37.15 (SPI_MCLK), Y5.3 (OUT)
GND: C97.2, C98.2, C99.2, C100.2, C101.2, C102.2, C103.2, C104.2, C105.2, C106.2, C107.2, C108.2, J92.2, J93.2, U37.3 (GND), Y5.2 (GND); also elsewhere on the board
unnamed: D73.C, U37.7 (LDR_2)
unnamed: C104.1, U37.12 (VDDA18_I/O)
unnamed: C102.1, U37.11 (VDDAY_I/O)
unnamed: C100.1, U37.10 (VDDA_I/O)

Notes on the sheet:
I²C: 1110011

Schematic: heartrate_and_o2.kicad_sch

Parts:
C41, C44: 100nF; C_0402_1005Metric
C42: 10µF; C_0402_1005Metric
C43: 4.7µF; C_0402_1005Metric
J50, J51, J53: Conn_01x02_Pin; PinHeader_1x02_P1.27mm_Vertical
J52: Conn_01x01_Pin; PinHeader_1x01_P1.27mm_Vertical
U16: MAX30101EFD_T; PSON80P560X330X165-14N; PARTREV 2

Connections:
+1V8: C43.1, C44.1, J51.1, U16.11 (VDD); also elsewhere on the board
+4V5: C41.1, C42.1, J50.1, U16.9 (VLED+); also elsewhere on the board
/Heartrate & O₂/HRINT1V8: J52.1, U16.13 (~INT)
/Heartrate & O₂/SCL1V8: J53.1, U16.2 (SCL)
/Heartrate & O₂/SDA1V8: J53.2, U16.3 (SDA)
GND: C41.2, C42.2, C43.2, C44.2, J50.2, J51.2, U16.4 (PGND), U16.12 (GND); also elsewhere on the board

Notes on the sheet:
I²C: 1010111

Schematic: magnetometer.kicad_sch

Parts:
C45: 4.7µF; C_0402_1005Metric
C46, C47: 1µF; C_0402_1005Metric
J54, J55, J56: Conn_01x02_Pin; PinHeader_1x02_P1.27mm_Vertical
U17: MMC34160PJ; XDCR_MMC34160PJ; PARTREV C

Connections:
+1V8: C47.1, J55.1, U17.12 (VDA); also elsewhere on the board
/Magnetometer/SCL: J56.1, U17.3 (SCL)
/Magnetometer/SDA: J56.2, U17.4 (SDA)
GND: C45.2, C46.2, C47.2, J54.2, J55.2, U17.11 (VSA); also elsewhere on the board
unnamed: C45.1, U17.8 (CAP)

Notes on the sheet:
I²C: 0110000

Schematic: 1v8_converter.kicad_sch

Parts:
C61, C62: 1µF; C_0402_1005Metric
J67: Conn_01x02_Pin; PinHeader_1x02_P1.27mm_Vertical
J68: Conn_02x08_Odd_Even; PinHeader_2x08_P1.27mm_Vertical
U25: TPS7A2018PDQNR; VREG_TPS7A2018PDQNR; PARTREV H

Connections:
+1V8: C62.1, J68.1, J68.3, J68.5, J68.7, J68.9, J68.11, J68.13, J68.15, U25.1 (OUT); also elsewhere on the board
+4V5: C61.1, J67.1, U25.3 (EN), U25.4 (IN); also elsewhere on the board
GND: C61.2, C62.2, J67.2, J68.2, J68.4, J68.6, J68.8, J68.10, J68.12, J68.14, J68.16, U25.2 (GND), U25.5 (EXP); also elsewhere on the board
